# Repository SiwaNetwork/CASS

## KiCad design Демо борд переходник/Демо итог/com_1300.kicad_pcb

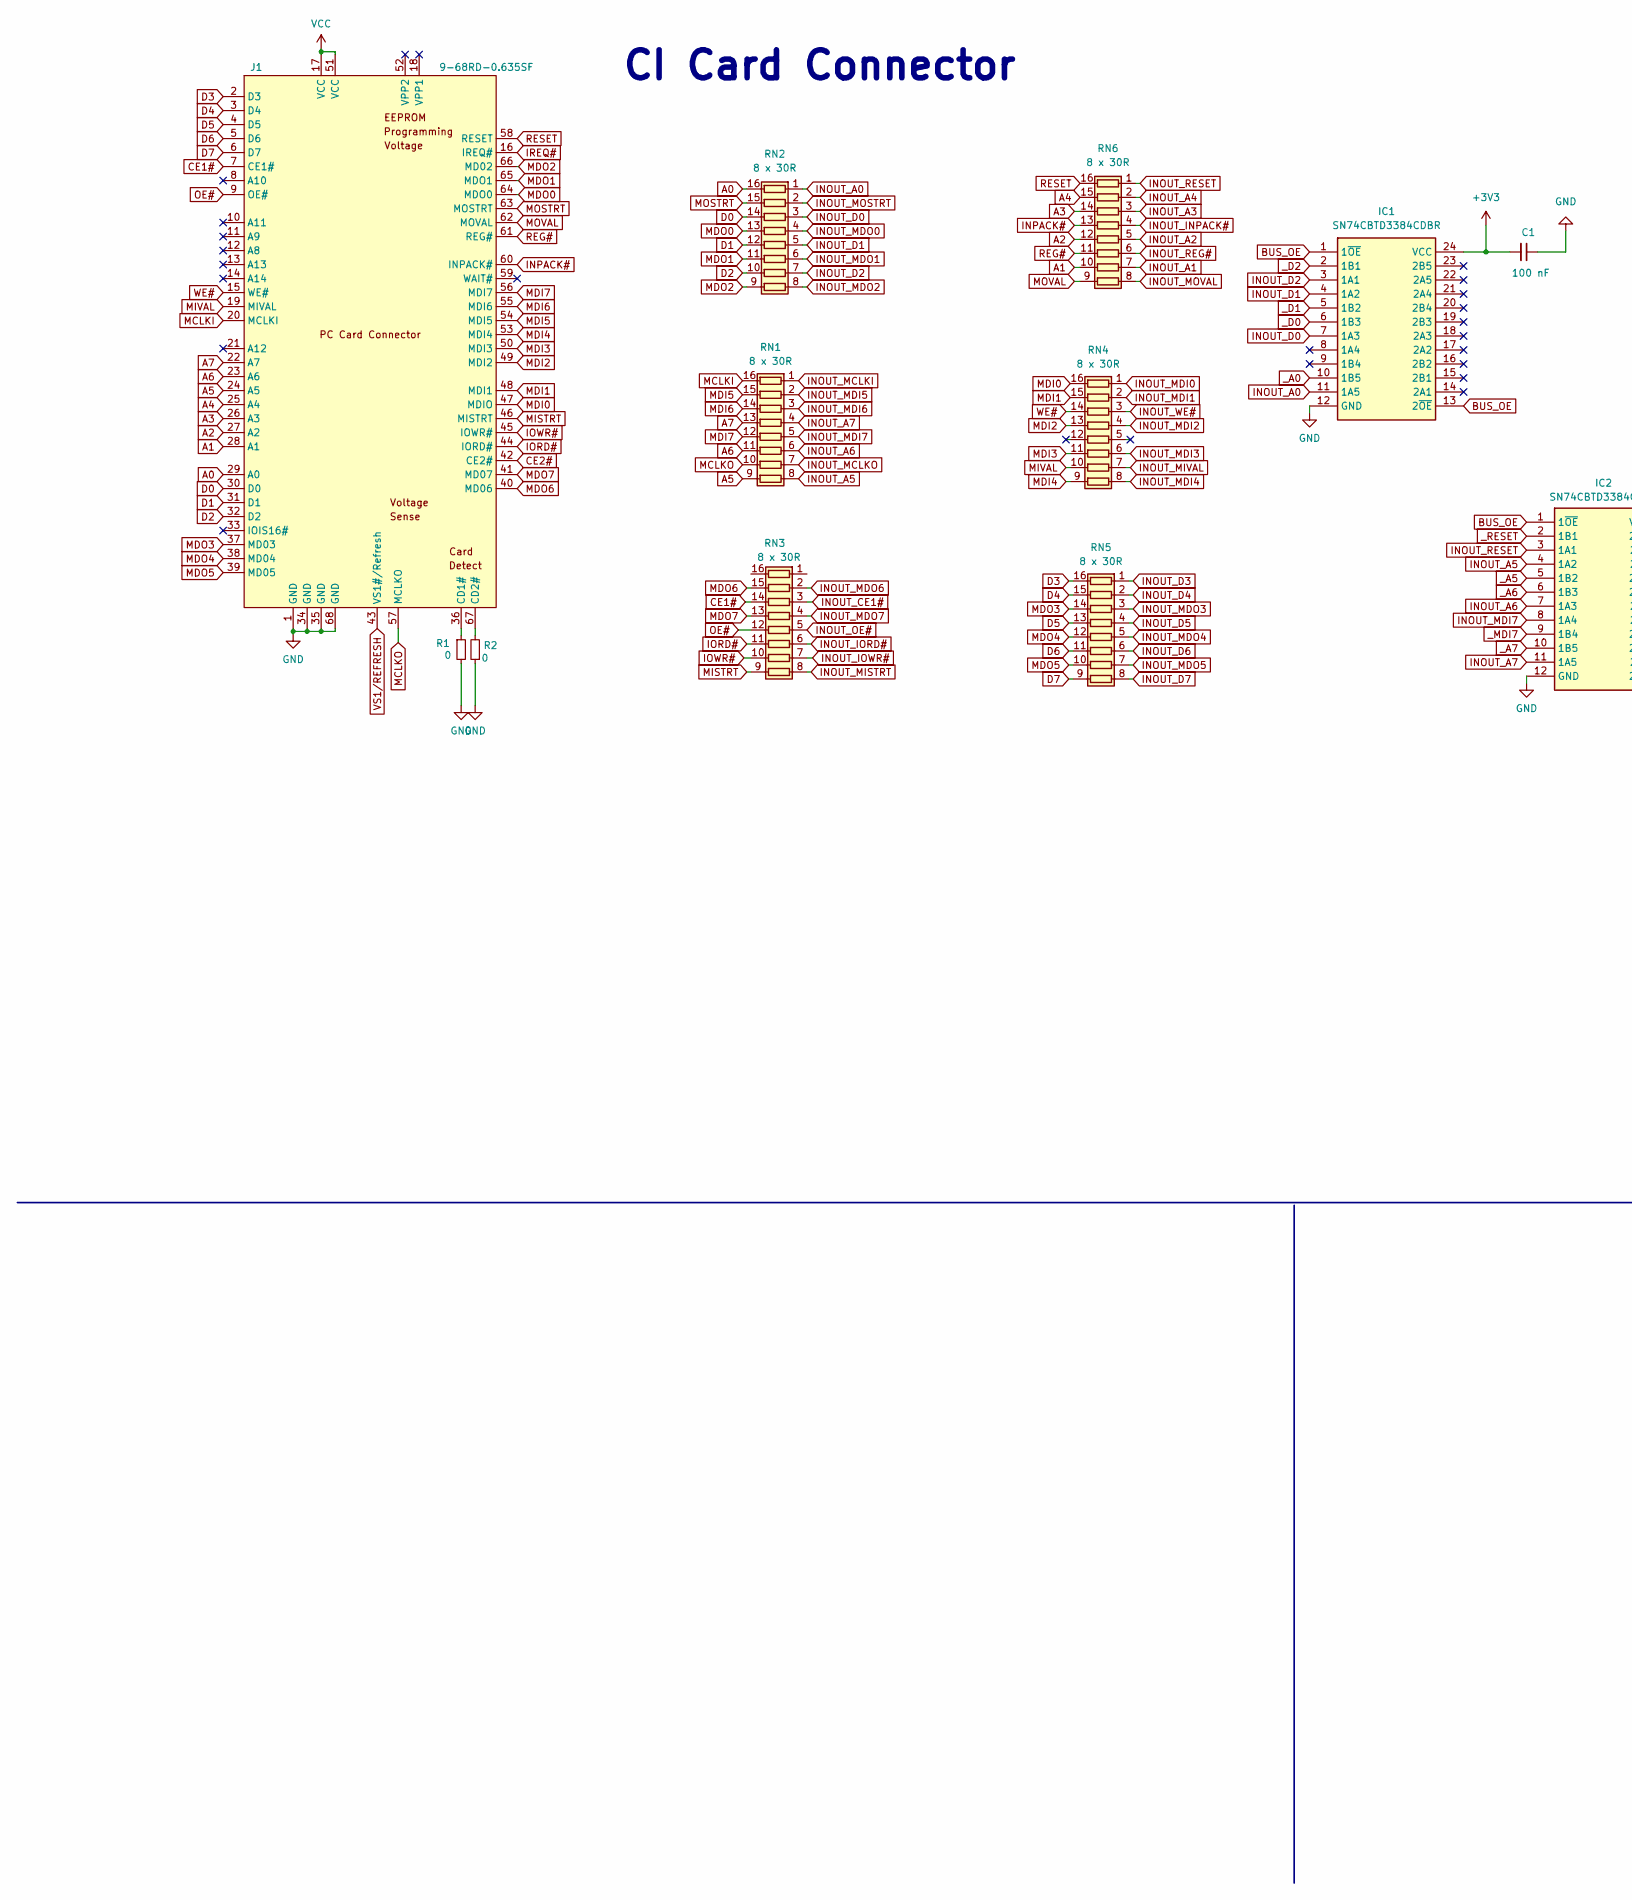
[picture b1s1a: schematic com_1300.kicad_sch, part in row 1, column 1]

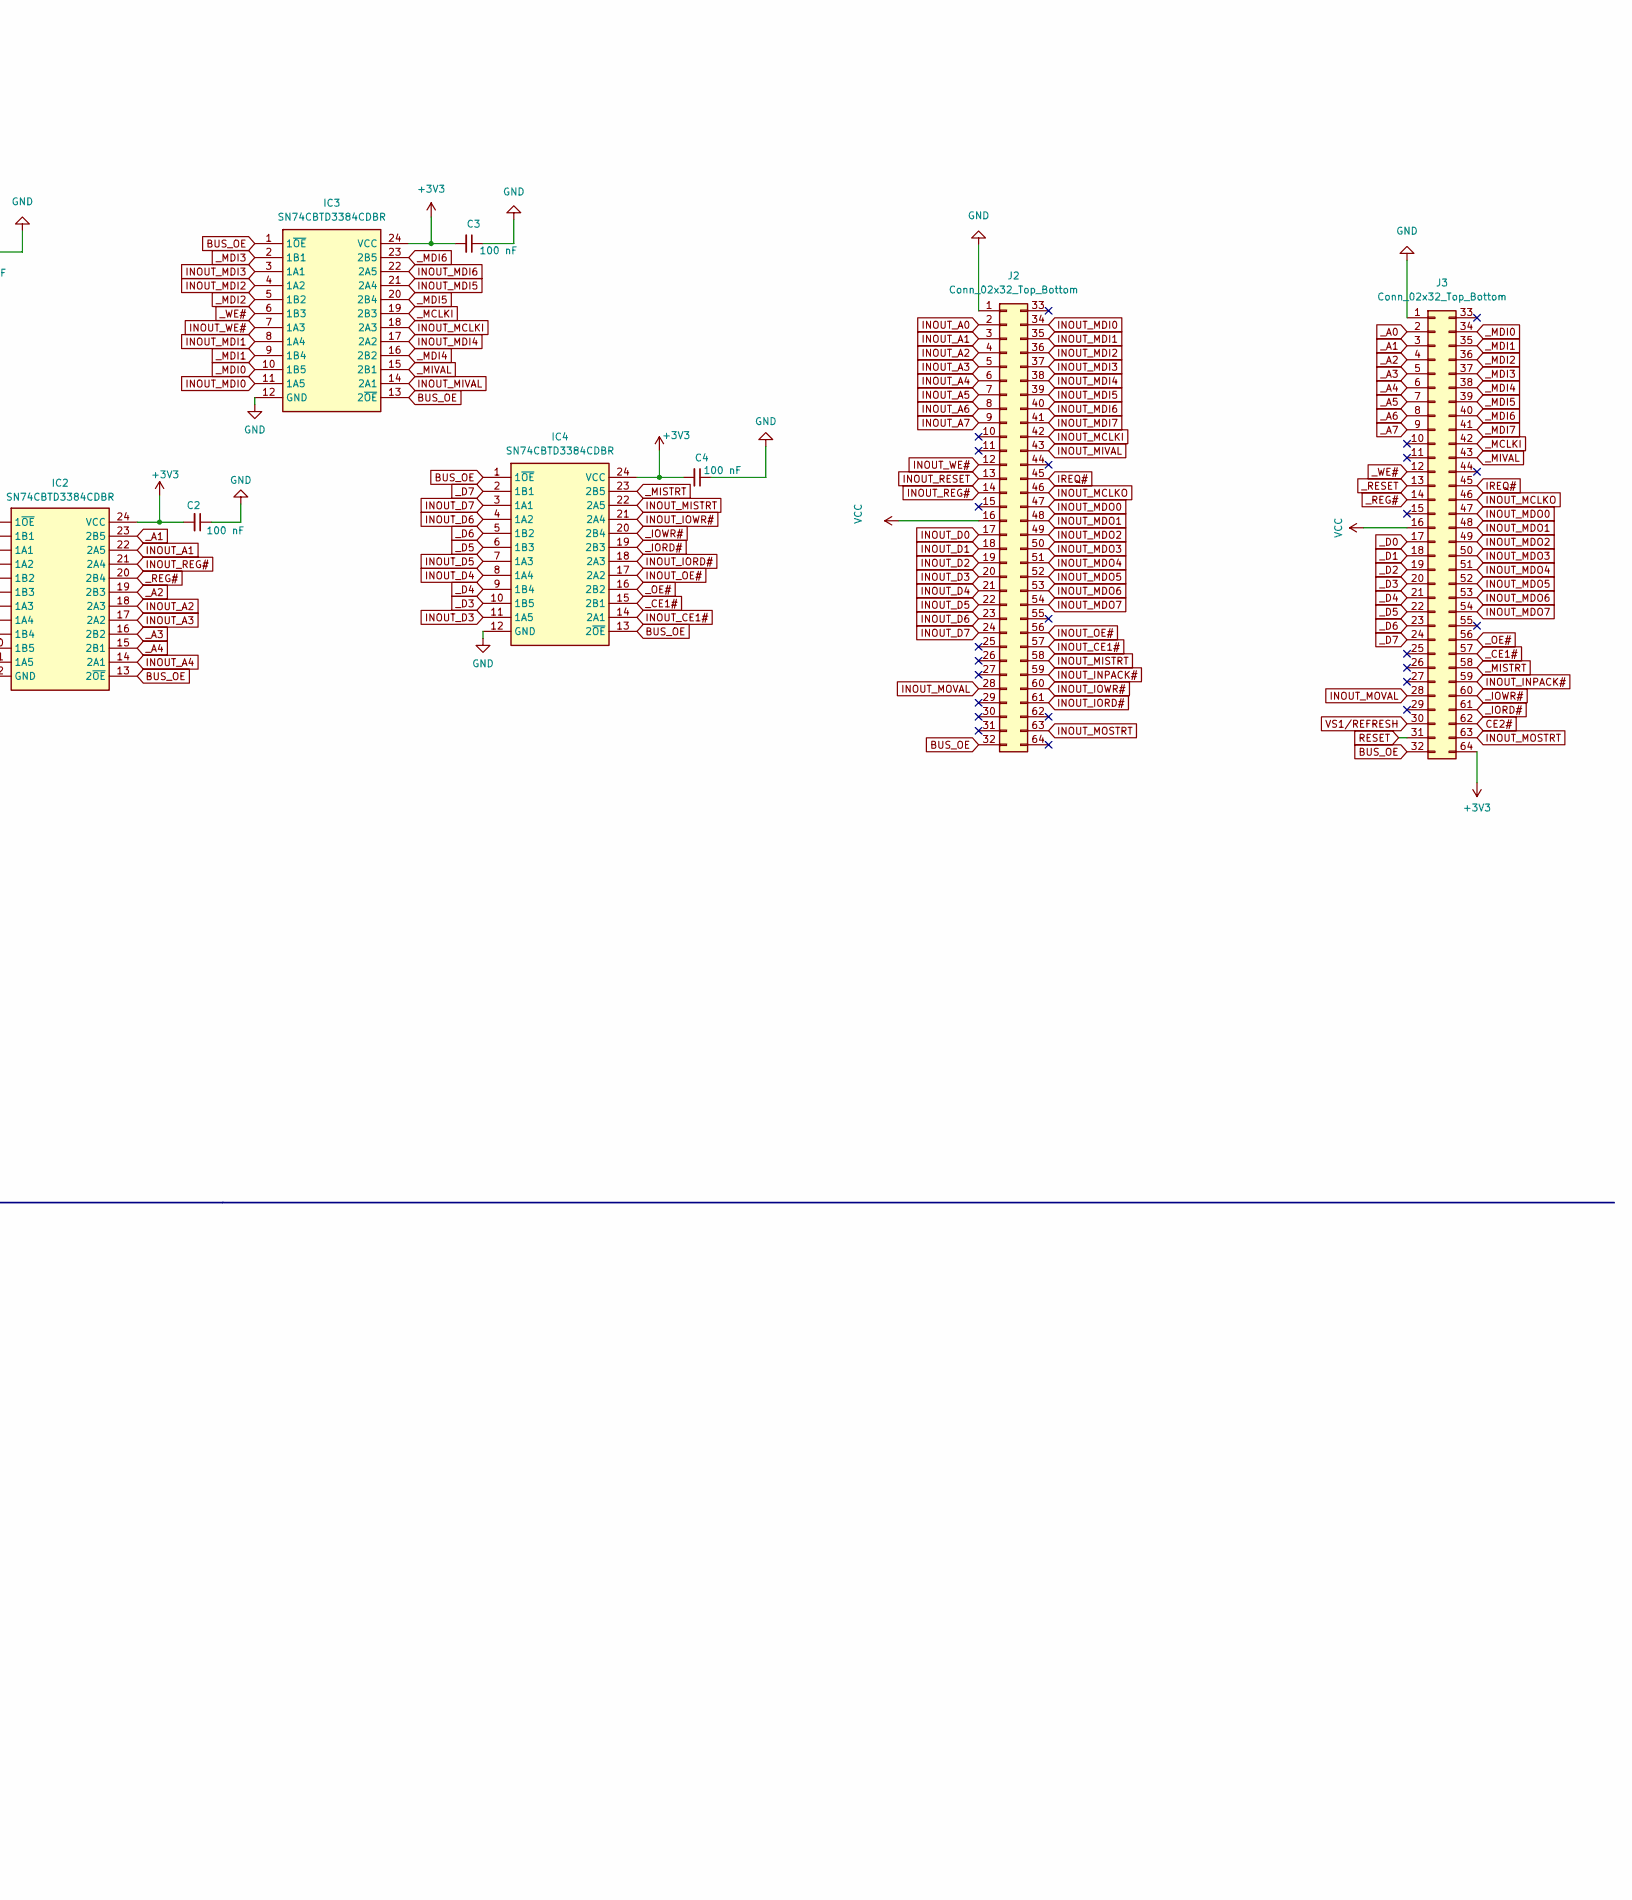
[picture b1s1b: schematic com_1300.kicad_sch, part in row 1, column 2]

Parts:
C1, C2, C3, C4: 100 nF; C_0201_0603Metric
IC1, IC2, IC3, IC4: SN74CBTD3384CDBR; SOP65P780X200-24N; Manufacturer_Part_Number SN74CBTD3384CDBR; Mouser Part Number 595-SN74CBTD3384CDBR
J1: 9-68RD-0.635SF; IC9_Series
J2, J3: Conn_02x32_Top_Bottom; PinHeader_2x32_P1.27mm_Horizontal
R1, R2: 0; R_0201_0603Metric
RN1, RN2, RN3, RN4, RN5, RN6: 8 x 30R; R_Cat16-8

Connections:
+3V3: C1.2, C2.2, C3.2, C4.2, IC1.24 (VCC), IC2.24 (VCC), IC3.24 (VCC), IC4.24 (VCC), J3.64
A0: J1.29 (A0), RN2.16 (R1.2)
A1: J1.28 (A1), RN6.10 (R7.2)
A2: J1.27 (A2), RN6.12 (R5.2)
A3: J1.26 (A3), RN6.14 (R3.2)
A4: J1.25 (A4), RN6.15 (R2.2)
A5: J1.24 (A5), RN1.9 (R8.2)
A6: J1.23 (A6), RN1.11 (R6.2)
A7: J1.22 (A7), RN1.13 (R4.2)
BUS_OE: IC1.1 (1~OE), IC1.13 (2~OE), IC2.1 (1~OE), IC2.13 (2~OE), IC3.1 (1~OE), IC3.13 (2~OE), IC4.1 (1~OE), IC4.13 (2~OE), J2.32, J3.32
CE1#: J1.7 (CE1#), RN3.14 (R3.2)
CE2#: J1.42 (CE2#), J3.62
D0: J1.30 (D0), RN2.14 (R3.2)
D1: J1.31 (D1), RN2.12 (R5.2)
D2: J1.32 (D2), RN2.10 (R7.2)
D3: J1.2 (D3), RN5.16 (R1.2)
D4: J1.3 (D4), RN5.15 (R2.2)
D5: J1.4 (D5), RN5.13 (R4.2)
D6: J1.5 (D6), RN5.11 (R6.2)
D7: J1.6 (D7), RN5.9 (R8.2)
GND: C1.1, C2.1, C3.1, C4.1, IC1.12 (GND), IC2.12 (GND), IC3.12 (GND), IC4.12 (GND), J1.1 (GND), J1.34 (GND), J1.35 (GND), J1.68 (GND), J2.1, J3.1, R1.2, R2.1
INOUT_A0: IC1.11 (1A5), J2.2, RN2.1 (R1.1)
INOUT_A1: IC2.22 (2A5), J2.3, RN6.7 (R7.1)
INOUT_A2: IC2.18 (2A3), J2.4, RN6.5 (R5.1)
INOUT_A3: IC2.17 (2A2), J2.5, RN6.3 (R3.1)
INOUT_A4: IC2.14 (2A1), J2.6, RN6.2 (R2.1)
INOUT_A5: IC2.4 (1A2), J2.7, RN1.8 (R8.1)
INOUT_A6: IC2.7 (1A3), J2.8, RN1.6 (R6.1)
INOUT_A7: IC2.11 (1A5), J2.9, RN1.4 (R4.1)
INOUT_CE1#: IC4.14 (2A1), J2.57, RN3.3 (R3.1)
INOUT_D0: IC1.7 (1A3), J2.17, RN2.3 (R3.1)
INOUT_D1: IC1.4 (1A2), J2.18, RN2.5 (R5.1)
INOUT_D2: IC1.3 (1A1), J2.19, RN2.7 (R7.1)
INOUT_D3: IC4.11 (1A5), J2.20, RN5.1 (R1.1)
INOUT_D4: IC4.8 (1A4), J2.21, RN5.2 (R2.1)
INOUT_D5: IC4.7 (1A3), J2.22, RN5.4 (R4.1)
INOUT_D6: IC4.4 (1A2), J2.23, RN5.6 (R6.1)
INOUT_D7: IC4.3 (1A1), J2.24, RN5.8 (R8.1)
INOUT_INPACK#: J2.59, J3.59, RN6.4 (R4.1)
INOUT_IORD#: IC4.18 (2A3), J2.61, RN3.6 (R6.1)
INOUT_IOWR#: IC4.21 (2A4), J2.60, RN3.7 (R7.1)
INOUT_MCLKI: IC3.18 (2A3), J2.42, RN1.1 (R1.1)
INOUT_MCLKO: J2.46, J3.46, RN1.7 (R7.1)
INOUT_MDI0: IC3.11 (1A5), J2.34, RN4.1 (R1.1)
INOUT_MDI1: IC3.8 (1A4), J2.35, RN4.2 (R2.1)
INOUT_MDI2: IC3.4 (1A2), J2.36, RN4.4 (R4.1)
INOUT_MDI3: IC3.3 (1A1), J2.37, RN4.6 (R6.1)
INOUT_MDI4: IC3.17 (2A2), J2.38, RN4.8 (R8.1)
INOUT_MDI5: IC3.21 (2A4), J2.39, RN1.2 (R2.1)
INOUT_MDI6: IC3.22 (2A5), J2.40, RN1.3 (R3.1)
INOUT_MDI7: IC2.8 (1A4), J2.41, RN1.5 (R5.1)
INOUT_MDO0: J2.47, J3.47, RN2.4 (R4.1)
INOUT_MDO1: J2.48, J3.48, RN2.6 (R6.1)
INOUT_MDO2: J2.49, J3.49, RN2.8 (R8.1)
INOUT_MDO3: J2.50, J3.50, RN5.3 (R3.1)
INOUT_MDO4: J2.51, J3.51, RN5.5 (R5.1)
INOUT_MDO5: J2.52, J3.52, RN5.7 (R7.1)
INOUT_MDO6: J2.53, J3.53, RN3.2 (R2.1)
INOUT_MDO7: J2.54, J3.54, RN3.4 (R4.1)
INOUT_MISTRT: IC4.22 (2A5), J2.58, RN3.8 (R8.1)
INOUT_MIVAL: IC3.14 (2A1), J2.43, RN4.7 (R7.1)
INOUT_MOSTRT: J2.63, J3.63, RN2.2 (R2.1)
INOUT_MOVAL: J2.28, J3.28, RN6.8 (R8.1)
INOUT_OE#: IC4.17 (2A2), J2.56, RN3.5 (R5.1)
INOUT_REG#: IC2.21 (2A4), J2.14, RN6.6 (R6.1)
INOUT_RESET: IC2.3 (1A1), J2.13, RN6.1 (R1.1)
INOUT_WE#: IC3.7 (1A3), J2.12, RN4.3 (R3.1)
INPACK#: J1.60 (INPACK#), RN6.13 (R4.2)
IORD#: J1.44 (IORD#), RN3.11 (R6.2)
IOWR#: J1.45 (IOWR#), RN3.10 (R7.2)
IREQ#: J1.16 (IREQ#), J2.45, J3.45
MCLKI: J1.20 (MCLKI), RN1.16 (R1.2)
MCLKO: J1.57 (MCLKO), RN1.10 (R7.2)
MDI0: J1.47 (MDIO), RN4.16 (R1.2)
MDI1: J1.48 (MDI1), RN4.15 (R2.2)
MDI2: J1.49 (MDI2), RN4.13 (R4.2)
MDI3: J1.50 (MDI3), RN4.11 (R6.2)
MDI4: J1.53 (MDI4), RN4.9 (R8.2)
MDI5: J1.54 (MDI5), RN1.15 (R2.2)
MDI6: J1.55 (MDI6), RN1.14 (R3.2)
MDI7: J1.56 (MDI7), RN1.12 (R5.2)
MDO0: J1.64 (MDO0), RN2.13 (R4.2)
MDO1: J1.65 (MDO1), RN2.11 (R6.2)
MDO2: J1.66 (MD02), RN2.9 (R8.2)
MDO3: J1.37 (MD03), RN5.14 (R3.2)
MDO4: J1.38 (MD04), RN5.12 (R5.2)
MDO5: J1.39 (MD05), RN5.10 (R7.2)
MDO6: J1.40 (MD06), RN3.15 (R2.2)
MDO7: J1.41 (MD07), RN3.13 (R4.2)
MISTRT: J1.46 (MISTRT), RN3.9 (R8.2)
MIVAL: J1.19 (MIVAL), RN4.10 (R7.2)
MOSTRT: J1.63 (MOSTRT), RN2.15 (R2.2)
MOVAL: J1.62 (MOVAL), RN6.9 (R8.2)
unnamed: J1.36 (CD1#), R1.1
unnamed: J1.67 (CD2#), R2.2
OE#: J1.9 (OE#), RN3.12 (R5.2)
REG#: J1.61 (REG#), RN6.11 (R6.2)
RESET: J1.58 (RESET), J3.31, RN6.16 (R1.2)
VCC: J1.17 (VCC), J1.51 (VCC), J2.16, J3.16
VS1/REFRESH: J1.43 (VS1#/Refresh), J3.30
WE#: J1.15 (WE#), RN4.14 (R3.2)
_A0: IC1.10 (1B5), J3.2
_A1: IC2.23 (2B5), J3.3
_A2: IC2.19 (2B3), J3.4
_A3: IC2.16 (2B2), J3.5
_A4: IC2.15 (2B1), J3.6
_A5: IC2.5 (1B2), J3.7
_A6: IC2.6 (1B3), J3.8
_A7: IC2.10 (1B5), J3.9
_CE1#: IC4.15 (2B1), J3.57
_D0: IC1.6 (1B3), J3.17
_D1: IC1.5 (1B2), J3.18
_D2: IC1.2 (1B1), J3.19
_D3: IC4.10 (1B5), J3.20
_D4: IC4.9 (1B4), J3.21
_D5: IC4.6 (1B3), J3.22
_D6: IC4.5 (1B2), J3.23
_D7: IC4.2 (1B1), J3.24
_IORD#: IC4.19 (2B3), J3.61
_IOWR#: IC4.20 (2B4), J3.60
_MCLKI: IC3.19 (2B3), J3.42
_MDI0: IC3.10 (1B5), J3.34
_MDI1: IC3.9 (1B4), J3.35
_MDI2: IC3.5 (1B2), J3.36
_MDI3: IC3.2 (1B1), J3.37
_MDI4: IC3.16 (2B2), J3.38
_MDI5: IC3.20 (2B4), J3.39
_MDI6: IC3.23 (2B5), J3.40
_MDI7: IC2.9 (1B4), J3.41
_MISTRT: IC4.23 (2B5), J3.58
_MIVAL: IC3.15 (2B1), J3.43
_OE#: IC4.16 (2B2), J3.56
_REG#: IC2.20 (2B4), J3.14
_RESET: IC2.2 (1B1), J3.13
_WE#: IC3.6 (1B3), J3.12

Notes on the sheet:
CI Card Connector

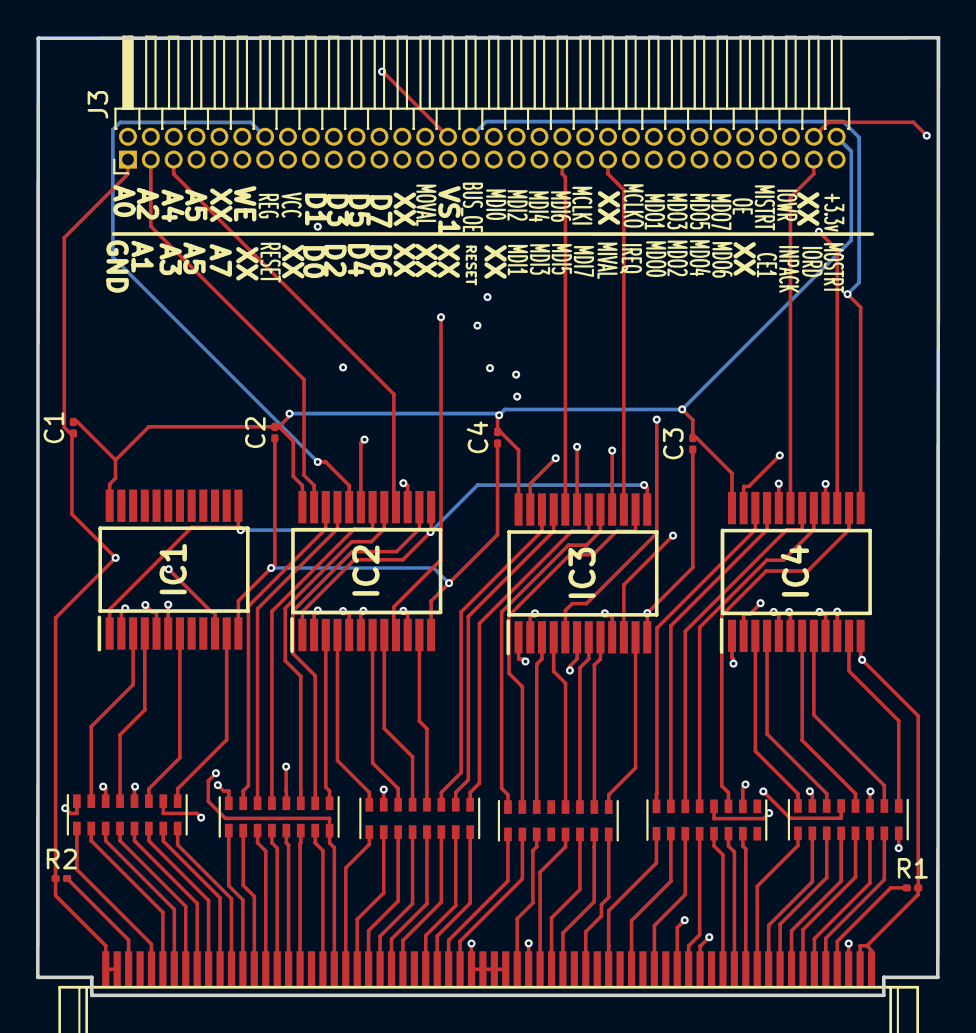
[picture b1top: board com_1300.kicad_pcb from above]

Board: 4 copper layers, 50.0 x 53.2 mm, 18 parts (0 on the bottom side), 135 nets.

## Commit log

2024-03-11 Redirekt
2024-03-11 Fabryk
2024-03-11 test
2024-03-16 dest
2024-03-26 bild
2024-03-27 apdate
2024-03-27 rename
2024-03-27 demo
2024-03-28 ignor
2024-03-30 dell
2024-03-30 joker
2024-03-31 010424
2024-04-01 020424
2024-04-02 22323
2024-04-02 124214
2024-04-03 234234
2024-04-05 234543
2024-04-07 2342342
2024-04-07 12312
2024-04-08 23623637
2024-04-08 2234545
2024-04-09 tracert
2024-04-11 566565
2024-04-11 453254\
2024-04-11 fdsdsf
2024-04-11 dfgdf
2024-04-12 23423
2024-04-16 32244
2024-04-19 3443
2024-05-08 12345
2024-05-28 PC Card
2024-07-13 board
2024-09-13 corpus
2024-09-23 2345
2025-01-16 23456789
2025-01-23 234567890
2025-02-07 test#
2025-02-11 update
    * PC Card standart files update with full name
    * add Jocker SCH and BOM
    * add CAM v2 (LATTICE)
2025-02-11 add CAM rev.2.0
    add CAM rev.2.0 LATTICE version
2025-02-11 update tree
2025-02-11 Create CAM_versions
    * добавлен файл с описанием версий
    * исправлено дерево
    * в2 это в1.1
    * в1.2.1 это в.1.3
2025-02-11 add v.1.3
2025-02-11 tree fix
2025-02-11 add v1.4
2025-02-15 updt rev.1.4
2025-02-16 тз на стенд
2025-02-24 cam 2.1 update
2025-03-04 LATTICE CAM update
    * CAM 2.0 обновлено обозначение LATTICE на схеме, сгенерирована схема
    * CAM 2.1 в работе. добавлен шинник внешнего программирования
2025-03-04 cam 2.0 update
2025-03-09 upd cam rev.2.1
2025-03-17 CAM rev.1.4 and 2.1 gerber and output update
2025-04-02 add rev. 2.01
2025-04-02 add CAM stand
2025-04-03 upd CAM rev2.01
2025-04-04 add lattice references
2025-04-04 upd CAM rev2.01
    добавлен сигнал PROGRAMN на T15
2025-04-04 upd CAM rev.2.01
2025-04-05 Удалил
2025-04-07 схема
2025-04-14 upd CAM 2.01 и CAM_STAND
    CAM 2.01
    - убраны ошибки трассировки
    - добавлены файлы для производства
    CAM_STAND
    - добавлен разъем JTAG для другой распиновки FPGA
    - трассировка закончена
2025-05-19 add CAM_LATTICE rev.2.02
    - изменена ширина платы до 49мм
2025-05-19 upd CAM_2.02
2025-05-27 ramka
2025-05-28 upd 2.02 files
2025-05-29 Добавил описание товаров, КД, ЭД
2025-06-02 очепятка
2025-07-09 sch upd
2025-09-01 upd
    - добавлен CAM V2.1
    - добавлен удлинитель CAM_EXT
2025-09-01 add CAM_DVB_CI_v.2.03
